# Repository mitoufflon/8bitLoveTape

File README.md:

# 8bitLoveTape
Attiny synth Based on 8bitMixTapeManila https://github.com/8BitMixtape/8BitMixtapeManila

https://vimeo.com/264154423

more info : https://ressources.labomedia.org/lovetape

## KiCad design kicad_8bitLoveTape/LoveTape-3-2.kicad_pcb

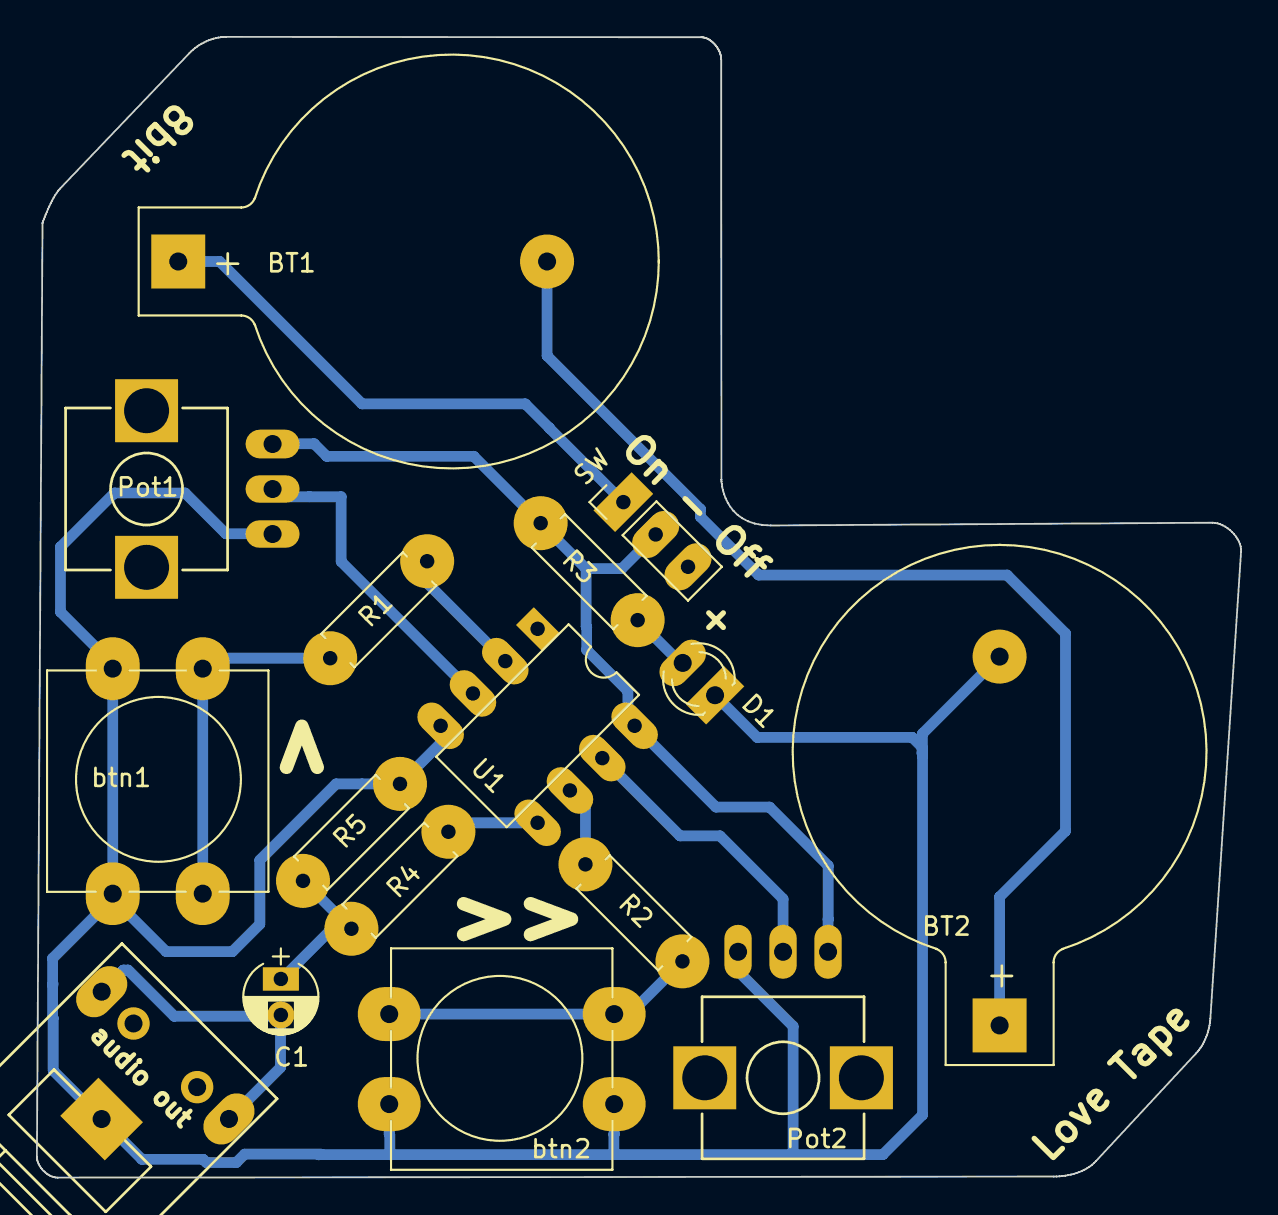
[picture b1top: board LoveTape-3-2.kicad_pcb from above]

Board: 2 copper layers, 66.9 x 63.4 mm, 16 parts (0 on the bottom side), 14 nets.

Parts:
BT1, BT2: Battery_Cell; Keystone_103_1x20mm-CoinCell
C1: CP1; CP_Radial_D4.0mm_P2.00mm
D1: LED; LED_D3.0mm_FlatTop
J1: audio out; Tayda_3.5mm_stereo_TRS_jack_A-853
Pot1: 10K lin; Potentiometer_Alpha-RV09
Pot2: 10k lin; Potentiometer_Alpha-RV09
R1: 12K; R_Axial_DIN0207_L6.3mm_D2.5mm_P7.62mm_Horizontal
R2: 12k; R_Axial_DIN0207_L6.3mm_D2.5mm_P7.62mm_Horizontal
R3: R; R_Axial_DIN0207_L6.3mm_D2.5mm_P7.62mm_Horizontal
R4: 3k3; R_Axial_DIN0207_L6.3mm_D2.5mm_P7.62mm_Horizontal
R5: 10k; R_Axial_DIN0207_L6.3mm_D2.5mm_P7.62mm_Horizontal
SW: On-Off; Pin_Header_Straight_1x03_Pitch2.54mm
U1: ATTINY85-20PU; DIP-8_W7.62mm
btn1, btn2: SW_PUSH; SW_PUSH-12mm

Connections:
GND: BT2.2, D1.1, J1.1, Pot1.1, Pot2.3, R5.2, U1.4, btn1.1, btn2.1
unnamed: C1.1, R4.2, R5.1
unnamed: C1.2, J1.2, J1.3
unnamed: BT1.1, SW.1
unnamed: BT1.2, BT2.1
unnamed: D1.2, R3.1
unnamed: Pot1.2, U1.3
unnamed: Pot2.2, U1.7
unnamed: R1.1, U1.2
unnamed: R1.2, btn1.2
unnamed: R2.1, U1.6
unnamed: R2.2, btn2.2
unnamed: R4.1, U1.5
VCC: Pot1.3, Pot2.1, R3.2, SW.2, U1.8

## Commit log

2018-02-20 Ajout dossier kicad
2018-02-20 Update README.md
    add link
2018-02-20 Update README.md
    add image!!!
2018-02-21 fix some bad routings...
2018-02-21 Create REAME.md
    add readme
2018-05-16 add V3
    Audio Output modification (-6dB/dc offset)
2018-05-16 Update README.md
    change image and url, add video link
2020-03-05 add code
2020-03-05 update link
